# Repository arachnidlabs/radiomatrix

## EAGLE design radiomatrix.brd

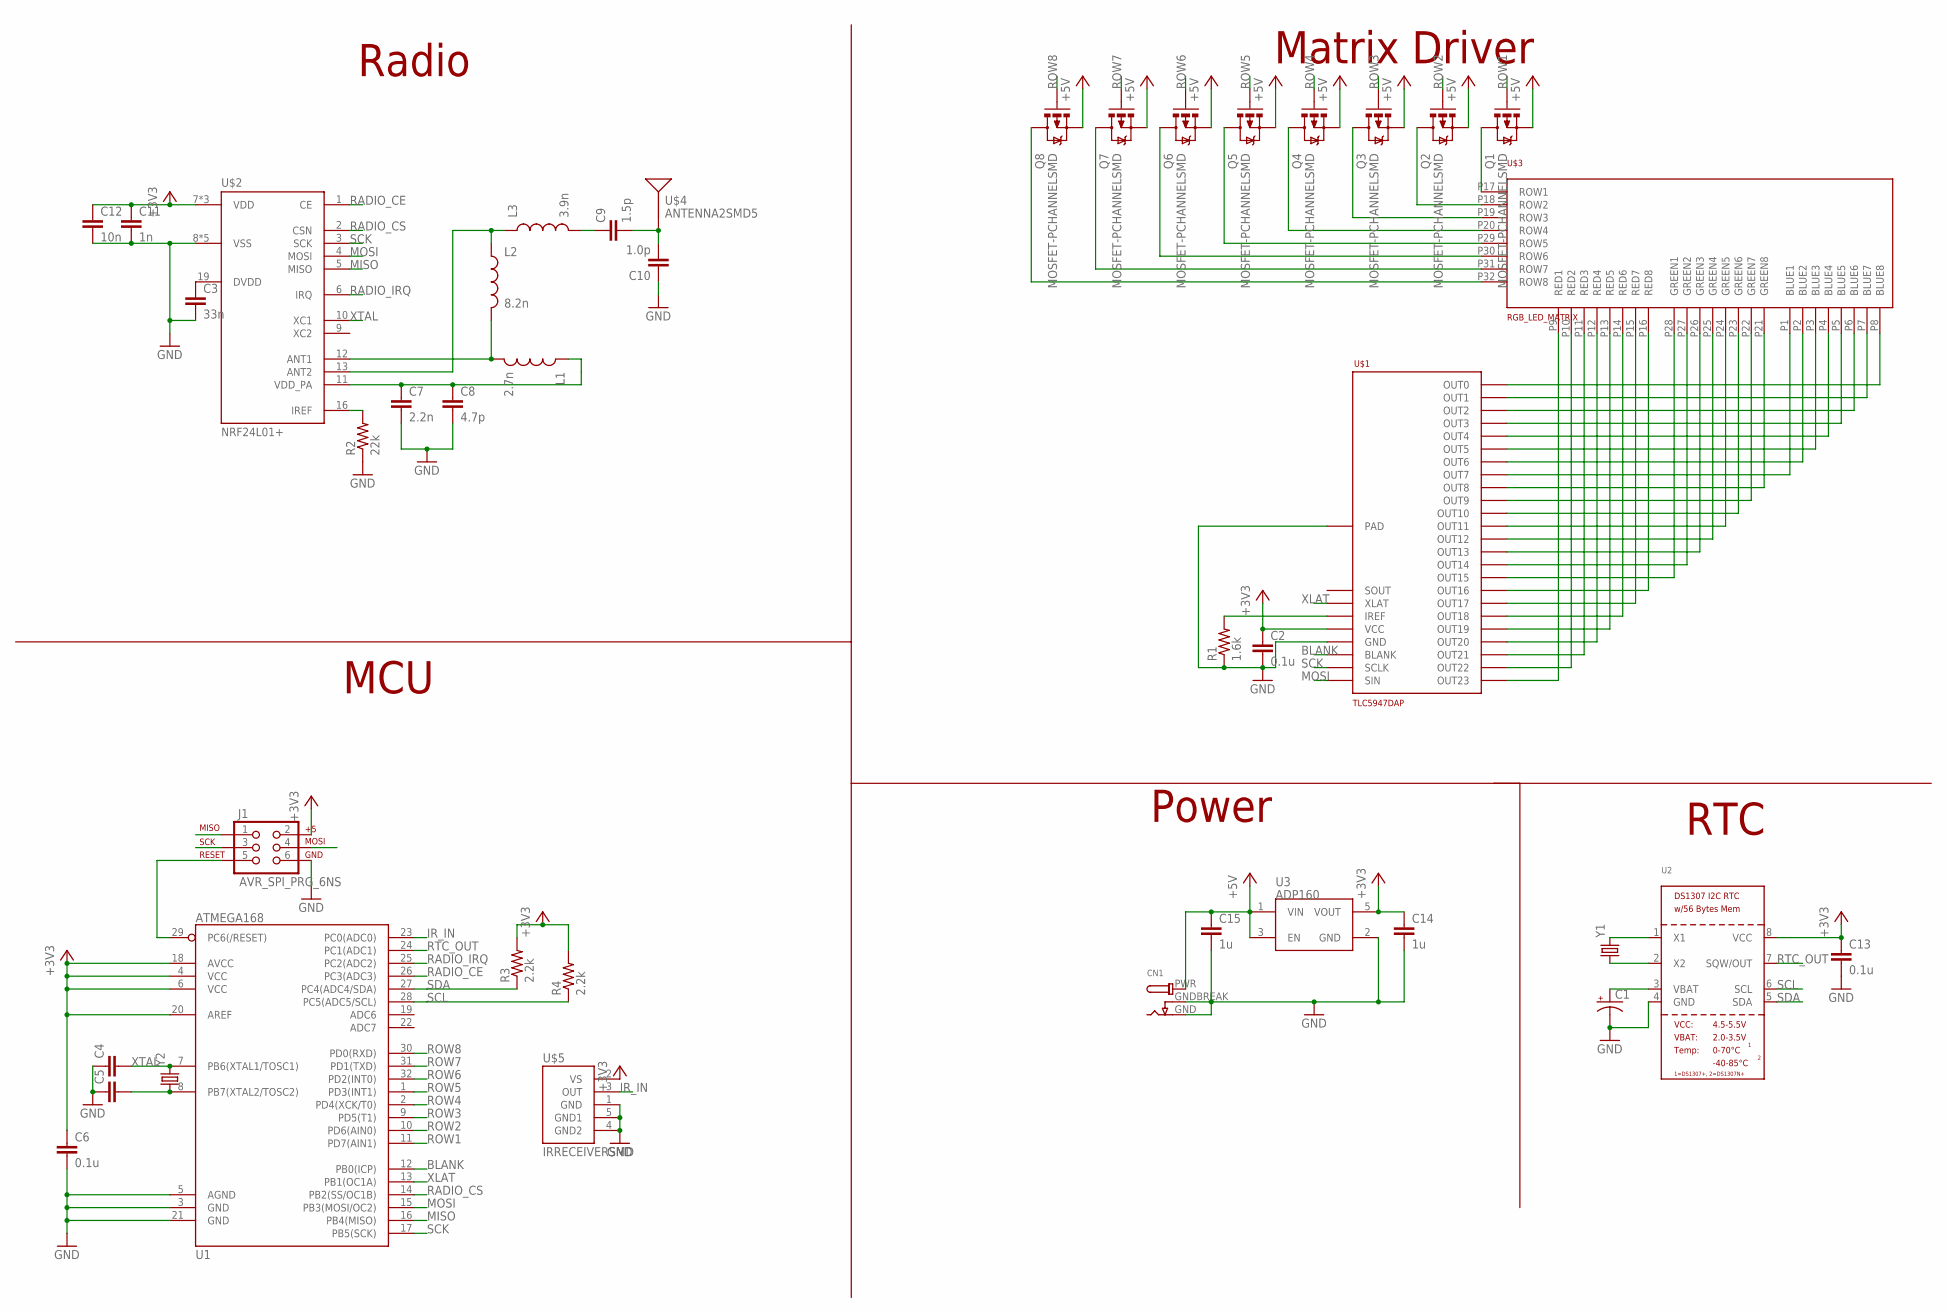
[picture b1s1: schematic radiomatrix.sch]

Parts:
C1: SUPERCAP; 414-VA5R
C2, C6, C13: 0.1u; 0603-CAP
C3: 33n; 0603-CAP
C4, C5: CAP0603-CAP; 0603-CAP
C7: 2.2n; 0603-CAP
C8: 4.7p; 0603-CAP
C9: 1.5p; 0603-CAP
C10: 1.0p; 0603-CAP
C11: 1n; 0603-CAP
C12: 10n; 0603-CAP
C14, C15: 1u; 0603-CAP
CN1: DCBARREL1.3MM; DCJACK_1.3MM_PTH
J1: AVR_SPI_PRG_6NS; 2X3-NS
L1: 2.7n; 0603
L2: 8.2n; 0603
L3: 3.9n; 0603
Q1, Q2, Q3, Q4, Q5, Q6, Q7, Q8: MOSFET-PCHANNELSMD; SOT23-3
R1: 1.6k; 0603-RES
R2: 22k; 0603-RES
R3, R4: 2.2k; 0603-RES
U1: ATMEGA168; TQFP32-08
U2: RTC_DS1307; SOIC8_150MIL
U3: ADP160; SOT23-5
U$1: TLC5947DAP; HTSSOP32DAP
U$2: NRF24L01+; QFN20
U$3: RGB_LED_MATRIX; RGB_LED_MATRIX_60MM
U$4: ANTENNA2SMD5; ANTENNA-CHIP5
U$5: IRRECEIVERSMD; TSOP8523
Y1: CRYSTAL32-SMD; CRYSTAL-32KHZ-SMD
Y2: CRYSTAL5X3; CRYSTAL-SMD-5X3

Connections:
+3V3: C2.1, C6.1, C11.1, C12.1, C13.1, C14.1, J1.2, R3.2, R4.2, U1.4 (VCC), U1.6 (VCC), U1.18 (AVCC), U1.20 (AREF), U2.8 (VCC), U3.5 (VOUT), U$1.32 (VCC), U$2.7 (VDD), U$2.15 (VDD), U$2.18 (VDD), U$5.2 (VS)
+5V: C15.1, CN1.PWR, Q1.2 (S), Q2.2 (S), Q3.2 (S), Q4.2 (S), Q5.2 (S), Q6.2 (S), Q7.2 (S), Q8.2 (S), U3.1 (VIN), U3.3 (EN)
ANT1: L1.2, L2.2, U$2.12 (ANT1)
ANT2: L2.1, L3.1, U$2.13 (ANT2)
ANT2B: C9.1, L3.2
ANT2C: C9.2, C10.2, U$4.FEED
BLANK: U1.12 (PB0(ICP)), U$1.2 (BLANK)
BLUE1: U$1.12 (OUT7), U$3.P1 (BLUE1)
BLUE2: U$1.11 (OUT6), U$3.P2 (BLUE2)
BLUE3: U$1.10 (OUT5), U$3.P3 (BLUE3)
BLUE4: U$1.9 (OUT4), U$3.P4 (BLUE4)
BLUE5: U$1.8 (OUT3), U$3.P5 (BLUE5)
BLUE6: U$1.7 (OUT2), U$3.P6 (BLUE6)
BLUE7: U$1.6 (OUT1), U$3.P7 (BLUE7)
BLUE8: U$1.5 (OUT0), U$3.P8 (BLUE8)
GND: C1.-, C2.2, C3.2, C4.1, C5.1, C6.2, C7.2, C8.2, C10.1, C11.2, C12.2, C13.2, C14.2, C15.2, CN1.GND, CN1.GNDBREAK, J1.6, R1.1, R2.1, U1.3 (GND), U1.5 (AGND), U1.21 (GND), U2.4 (GND), U3.2 (GND), U$1.1 (GND), U$1.EXP (PAD), U$2.8 (VSS), U$2.14 (VSS), U$2.17 (VSS), U$2.20 (VSS), U$2.EXP (VSS), U$5.1 (GND), U$5.4 (GND2), U$5.5 (GND1)
GREEN1: U$1.20 (OUT15), U$3.P28 (GREEN1)
GREEN2: U$1.19 (OUT14), U$3.P27 (GREEN2)
GREEN3: U$1.18 (OUT13), U$3.P26 (GREEN3)
GREEN4: U$1.17 (OUT12), U$3.P25 (GREEN4)
GREEN5: U$1.16 (OUT11), U$3.P24 (GREEN5)
GREEN6: U$1.15 (OUT10), U$3.P23 (GREEN6)
GREEN7: U$1.14 (OUT9), U$3.P22 (GREEN7)
GREEN8: U$1.13 (OUT8), U$3.P21 (GREEN8)
IR_IN: U1.23 (PC0(ADC0)), U$5.3 (OUT)
MISO: J1.1, U1.16 (PB4(MISO)), U$2.5 (MISO)
MOSI: J1.4, U1.15 (PB3(MOSI/OC2)), U$1.4 (SIN), U$2.4 (MOSI)
unnamed: C1.+, U2.3 (VBAT)
unnamed: U2.2 (X2), Y1.X1 (1)
unnamed: U2.1 (X1), Y1.X2 (2)
unnamed: R1.2, U$1.31 (IREF)
unnamed: C3.1, U$2.19 (DVDD)
unnamed: C7.1, C8.1, L1.1, U$2.11 (VDD_PA)
unnamed: C5.2, U1.8 (PB7(XTAL2/TOSC2)), Y2.1
unnamed: J1.5, U1.29 (PC6(/RESET))
unnamed: R2.2, U$2.16 (IREF)
R1: Q1.3 (D), U$3.P17 (ROW1)
R2: Q2.3 (D), U$3.P18 (ROW2)
R3: Q3.3 (D), U$3.P19 (ROW3)
R4: Q4.3 (D), U$3.P20 (ROW4)
R5: Q5.3 (D), U$3.P29 (ROW5)
R6: Q6.3 (D), U$3.P30 (ROW6)
R7: Q7.3 (D), U$3.P31 (ROW7)
R8: Q8.3 (D), U$3.P32 (ROW8)
RADIO_CE: U1.26 (PC3(ADC3)), U$2.1 (CE)
RADIO_CS: U1.14 (PB2(SS/OC1B)), U$2.2 (CSN)
RADIO_IRQ: U1.25 (PC2(ADC2)), U$2.6 (IRQ)
RED1: U$1.28 (OUT23), U$3.P9 (RED1)
RED2: U$1.27 (OUT22), U$3.P10 (RED2)
RED3: U$1.26 (OUT21), U$3.P11 (RED3)
RED4: U$1.25 (OUT20), U$3.P12 (RED4)
RED5: U$1.24 (OUT19), U$3.P13 (RED5)
RED6: U$1.23 (OUT18), U$3.P14 (RED6)
RED7: U$1.22 (OUT17), U$3.P15 (RED7)
RED8: U$1.21 (OUT16), U$3.P16 (RED8)
ROW1: Q1.1 (G), U1.11 (PD7(AIN1))
ROW2: Q2.1 (G), U1.10 (PD6(AIN0))
ROW3: Q3.1 (G), U1.9 (PD5(T1))
ROW4: Q4.1 (G), U1.2 (PD4(XCK/T0))
ROW5: Q5.1 (G), U1.1 (PD3(INT1))
ROW6: Q6.1 (G), U1.32 (PD2(INT0))
ROW7: Q7.1 (G), U1.31 (PD1(TXD))
ROW8: Q8.1 (G), U1.30 (PD0(RXD))
RTC_OUT: U1.24 (PC1(ADC1)), U2.7 (SQW/OUT)
SCK: J1.3, U1.17 (PB5(SCK)), U$1.3 (SCLK), U$2.3 (SCK)
SCL: R4.1, U1.28 (PC5(ADC5/SCL)), U2.6 (SCL)
SDA: R3.1, U1.27 (PC4(ADC4/SDA)), U2.5 (SDA)
XLAT: U1.13 (PB1(OC1A)), U$1.30 (XLAT)
XTAL: C4.2, U1.7 (PB6(XTAL1/TOSC1)), U$2.10 (XC1), Y2.3 (2)

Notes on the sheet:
MCU
Radio
Matrix Driver
Power
RTC

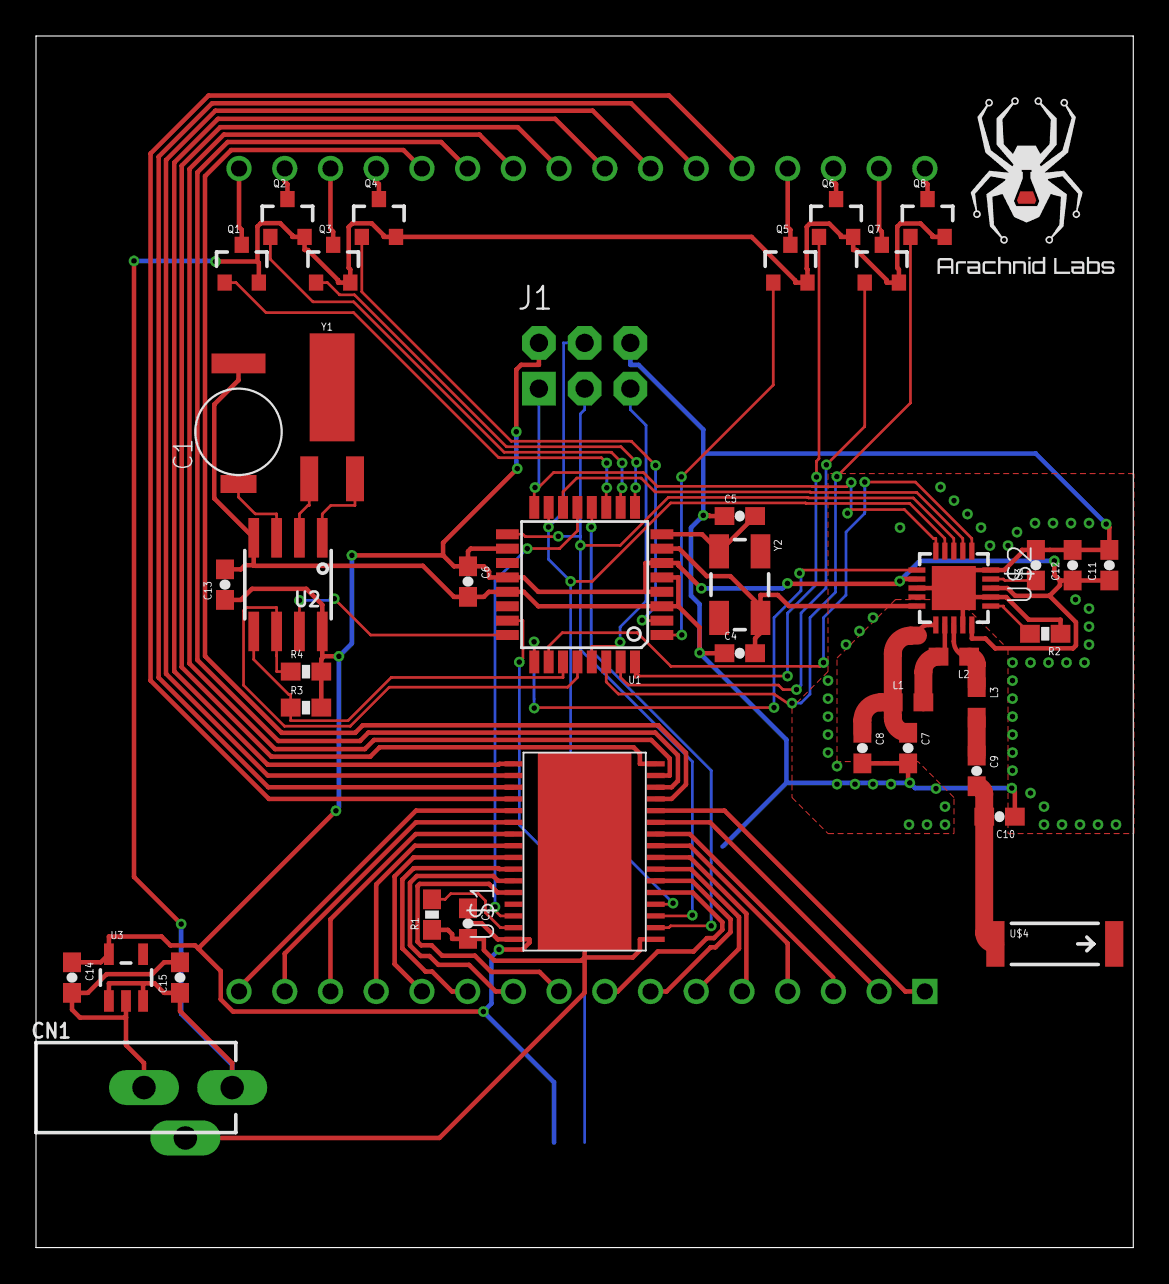
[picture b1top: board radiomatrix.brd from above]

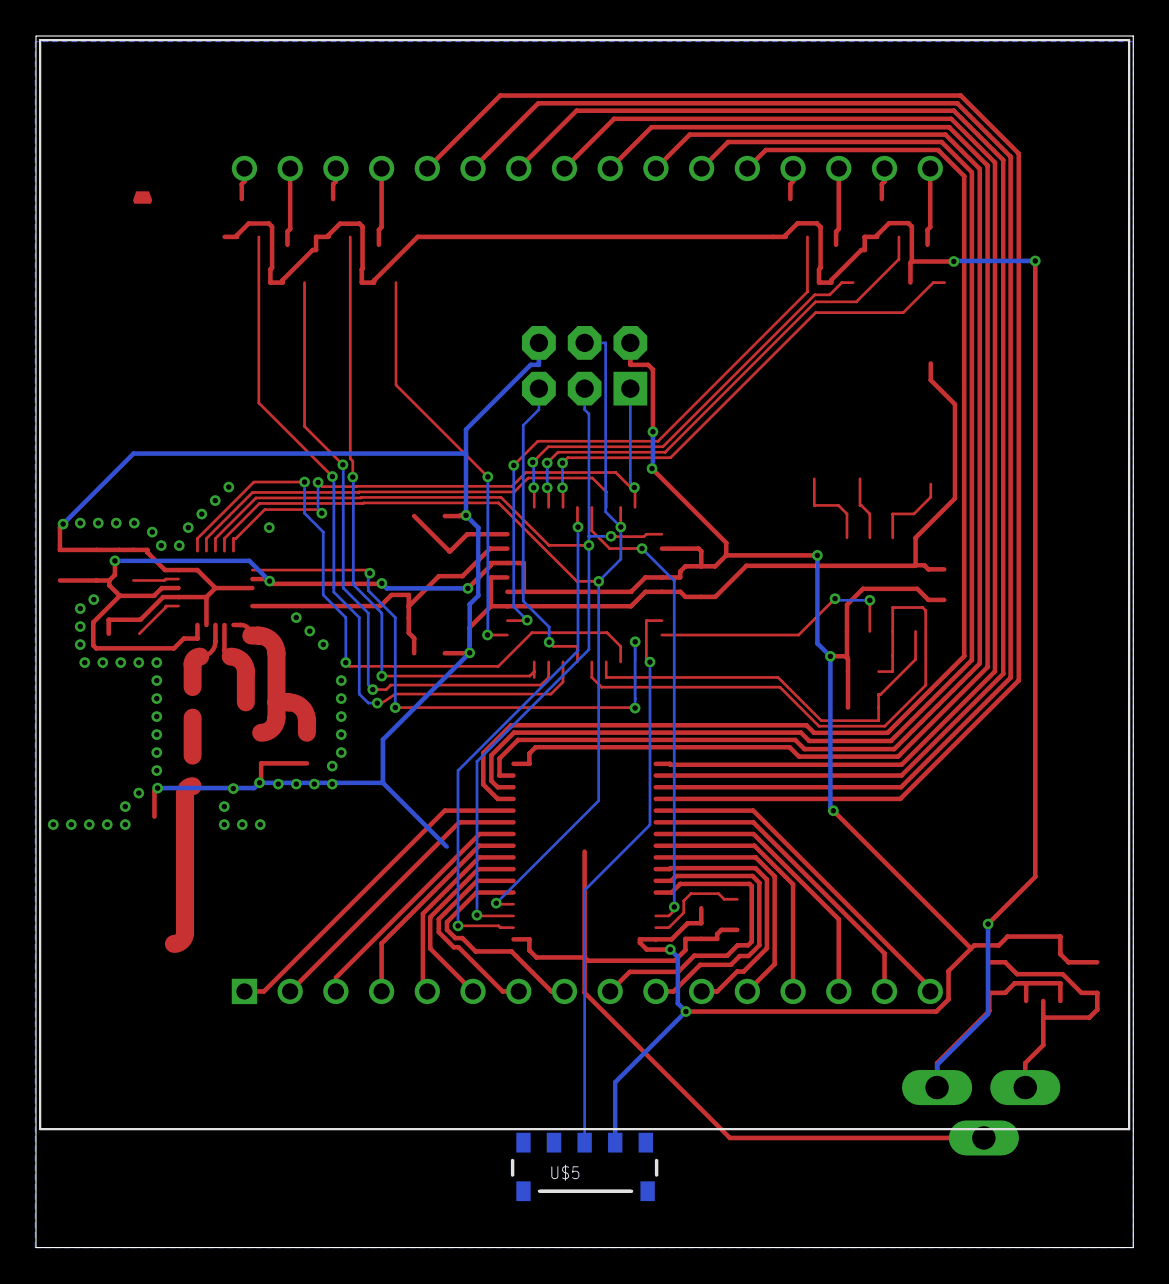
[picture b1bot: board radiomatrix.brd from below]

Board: 2 copper layers, 61.0 x 67.3 mm, 43 parts (2 on the bottom side), 69 nets.

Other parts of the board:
U$6: ARACHNID_LABS_LOGO_SM

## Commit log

2013-02-17 Initial commit.
2013-02-17 Cropped render image.

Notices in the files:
parts and their libraries:
SparkFun-DigitalIC: Licensing: CC v3.0 Share-Alike You are welcome to use this library for commercial purposes.
microbuilder: This work is placed in the public domain, and may be freely used for commercial and non-commercial work with the following conditions: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
